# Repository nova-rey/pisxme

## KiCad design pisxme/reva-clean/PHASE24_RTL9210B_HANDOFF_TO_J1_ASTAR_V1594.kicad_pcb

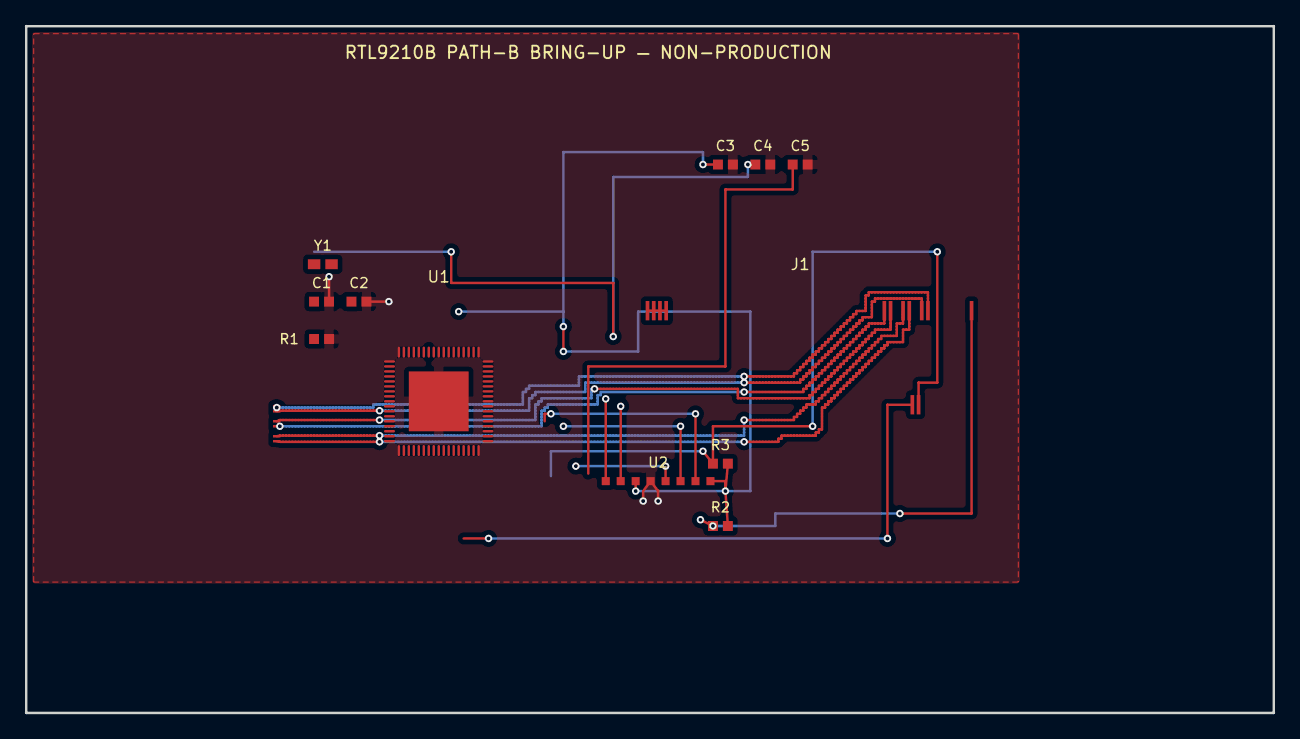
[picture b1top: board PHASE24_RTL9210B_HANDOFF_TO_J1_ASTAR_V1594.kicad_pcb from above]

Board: 6 copper layers, 100.1 x 55.1 mm, 13 parts (0 on the bottom side), 22 nets.

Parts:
C1: 16pF_XTAL_IN; BRINGUP_16pF_XTAL_IN
C2: 16pF_XTAL_OUT; BRINGUP_16pF_XTAL_OUT
C3: RTL_3V3_DEC; BRINGUP_RTL_3V3_DEC
C4: RTL_1V1_DEC; BRINGUP_RTL_1V1_DEC
C5: RTL_5V_DEC; BRINGUP_RTL_5V_DEC
J1: M.2 Socket 3 M-key 2280; BRINGUP_M2_MKEY
JH1: QFN_ESCAPE_HANDOFF
R1: 12k_RSET; BRINGUP_12k_RSET
R2: PEDET_PULLUP; BRINGUP_PEDET_PULLUP
R3: CLKREQ_PULLUP; BRINGUP_CLKREQ_PULLUP
U1: RTL9210B-CG; RTL9210B-CG_QUALIFICATION
U2: W25Q128_SPI_FLASH; BRINGUP_W25Q128_SPI_FLASH
Y1: XTAL_25MHz; BRINGUP_XTAL_25MHz

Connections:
CLKREQ_N: J1.52, R3.1, U1.13
GND: C1.2, C2.2, C3.2, C4.2, C5.2, R1.2, U1.45, U1.66, U1.69, U2.4
LANE0_RXN: J1.41, JH1.65, U1.65
LANE0_RXP: J1.43, JH1.64, U1.64
LANE0_TXN: J1.47, JH1.67, U1.67
LANE0_TXP: J1.49, JH1.68, U1.68
PEDET: J1.69, R2.1, U1.8
PERST_N: J1.50, U1.14
REFCLK_N: J1.53, JH1.62, U1.62
REFCLK_P: J1.55, JH1.61, U1.61
RSET: R1.1, U1.51
RTL_1V1: C4.1, U1.16, U1.25, U1.36, U1.40, U1.50, U1.55, U1.60, U1.63
RTL_3V3: C3.1, R2.2, R3.2, U1.20, U1.34, U1.39, U1.52, U2.3, U2.8
RTL_5V: C5.1, U1.17, U1.33
SPICLK: U1.19, U2.6
SPICS: U1.24, U2.1
SPISI: U1.18, U2.5
SPISO: U1.23, U2.2
SPISO3: U1.22, U2.7
SSD_3V3: J1.2, J1.4, J1.6, J1.8
XTAL_IN: C1.1, U1.53, Y1.1
XTAL_OUT: C2.1, U1.54, Y1.2

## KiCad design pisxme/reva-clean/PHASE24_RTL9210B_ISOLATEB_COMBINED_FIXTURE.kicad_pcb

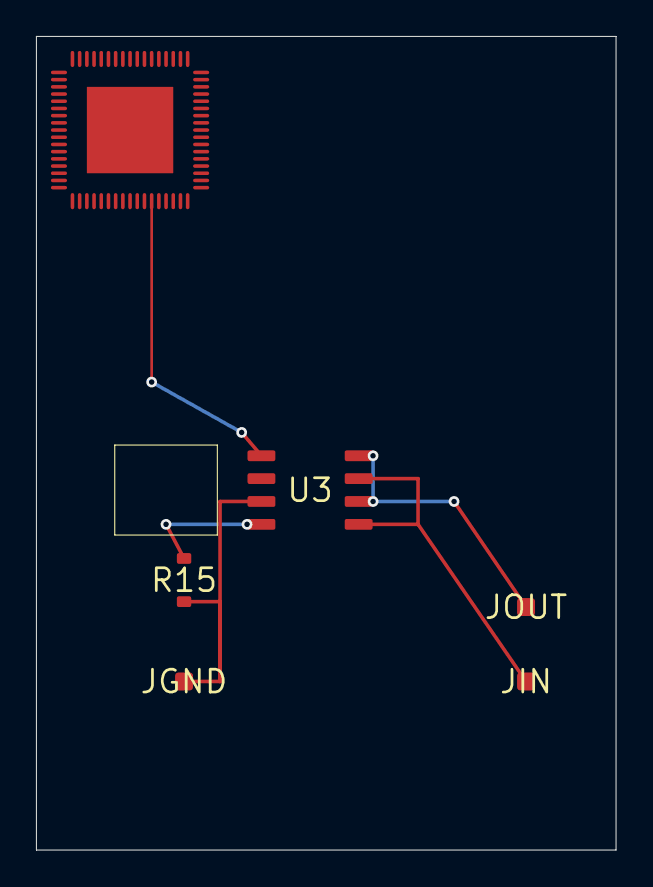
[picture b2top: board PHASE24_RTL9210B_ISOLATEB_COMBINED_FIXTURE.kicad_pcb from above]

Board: 6 copper layers, 32.2 x 45.2 mm, 6 parts (0 on the bottom side), 5 nets.

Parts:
JGND: GND_RETURN
JIN: SSD_3V3_SOURCE
JOUT: SSD_3V3_LOAD
R15: 76.8R_1PCT
U1: RTL9210B-CG; RTL9210B-CG_QUALIFICATION
U3: MIC2545A-1YM

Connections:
GND: JGND.1, R15.2, U3.3
ISOLATEB: U1.12, U3.1
MIC2545_ILIM: R15.1, U3.4
RTL_3V3: JIN.1, U3.5, U3.7
SSD_3V3: JOUT.1, U3.6, U3.8
